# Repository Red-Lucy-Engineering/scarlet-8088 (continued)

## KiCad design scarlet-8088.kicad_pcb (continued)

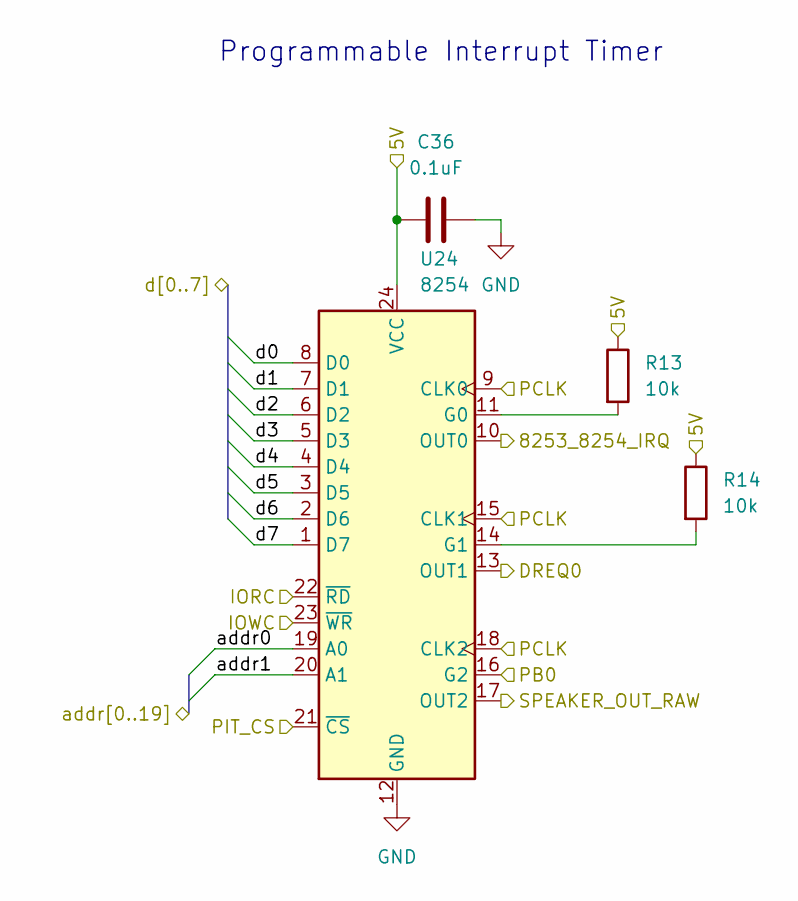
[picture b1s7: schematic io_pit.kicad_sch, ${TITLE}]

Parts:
C36: 0.1uF; C_Disc_D3.0mm_W1.6mm_P2.50mm
R13, R14: 10k; R_Axial_DIN0204_L3.6mm_D1.6mm_P5.08mm_Horizontal
U24: 8254; DIP-24_W15.24mm_Socket

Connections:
/5V: C36.1, R13.1, R14.1, U24.24 (VCC); also elsewhere on the board
/Compute/addr0: U24.19 (A0); also elsewhere on the board
/Compute/addr1: U24.20 (A1); also elsewhere on the board
/Compute/d0: U24.8 (D0); also elsewhere on the board
/Compute/d1: U24.7 (D1); also elsewhere on the board
/Compute/d2: U24.6 (D2); also elsewhere on the board
/Compute/d3: U24.5 (D3); also elsewhere on the board
/Compute/d4: U24.4 (D4); also elsewhere on the board
/Compute/d5: U24.3 (D5); also elsewhere on the board
/Compute/d6: U24.2 (D6); also elsewhere on the board
/Compute/d7: U24.1 (D7); also elsewhere on the board
/IO/8253_8254_IRQ: U24.10 (OUT0); also elsewhere on the board
/IO/PB0: U24.16 (G2); also elsewhere on the board
/IO/PIT_CS: U24.21 (~CS); also elsewhere on the board
/IO/Programmable Interrupt Timer/DREQ0: U24.13 (OUT1)
/IO/Programmable Interrupt Timer/SPEAKER_OUT_RAW: U24.17 (OUT2)
/IORC: U24.22 (~RD); also elsewhere on the board
/IOWC: U24.23 (~WR); also elsewhere on the board
/PCLK: U24.9 (CLK0), U24.15 (CLK1), U24.18 (CLK2); also elsewhere on the board
GND: C36.2, U24.12 (GND); also elsewhere on the board
unnamed: R13.2, U24.11 (G0)
unnamed: R14.2, U24.14 (G1)

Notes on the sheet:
Programmable Interrupt Timer

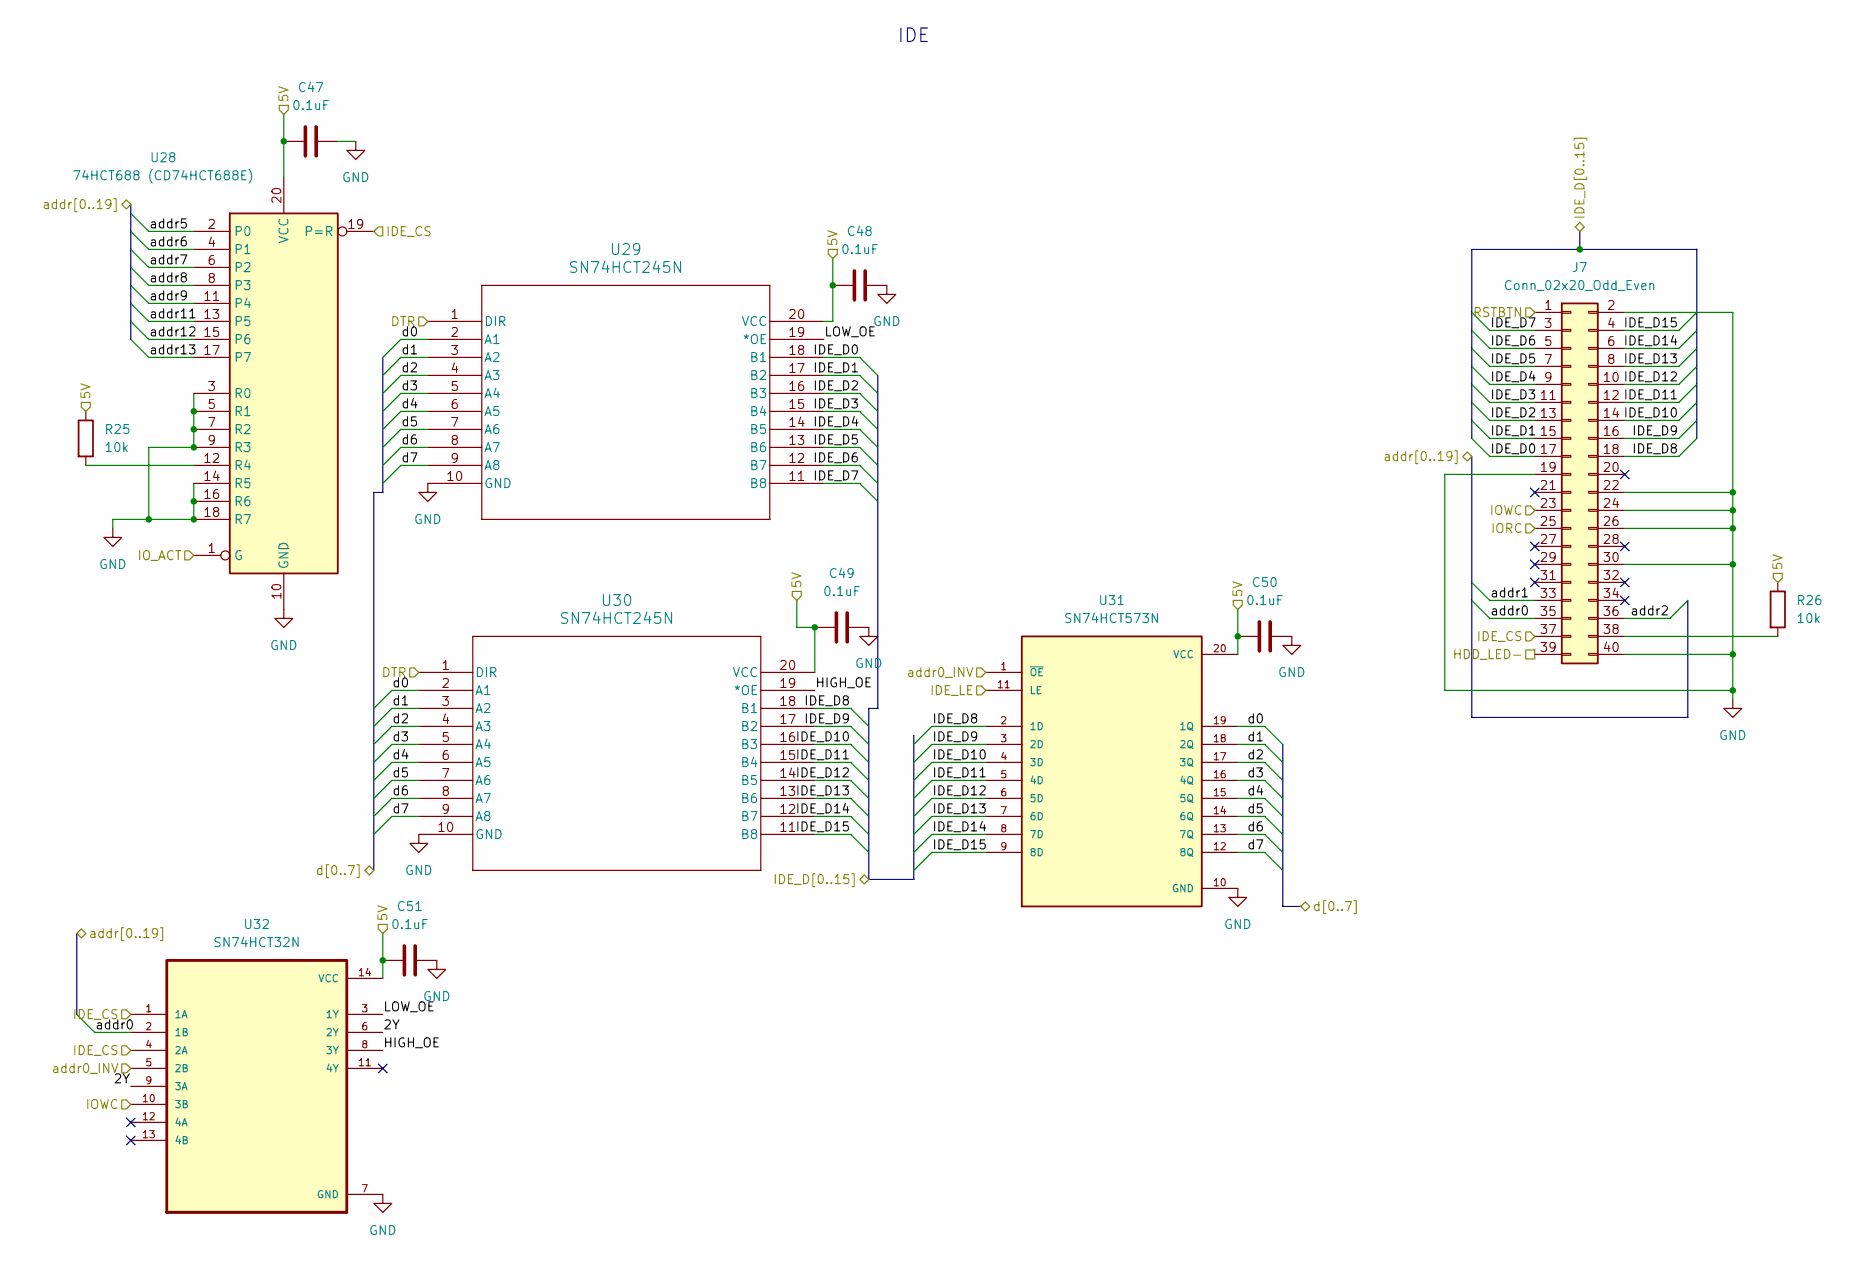
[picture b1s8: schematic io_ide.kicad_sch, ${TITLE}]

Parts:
C47, C48, C49, C50, C51: 0.1uF; C_Disc_D3.0mm_W1.6mm_P2.50mm
J7: Conn_02x20_Odd_Even; IDC-Header_2x20_P2.54mm_Vertical
R25, R26: 10k; R_Axial_DIN0204_L3.6mm_D1.6mm_P5.08mm_Horizontal
U28: 74HCT688 (CD74HCT688E); DIP-20_W7.62mm_Socket
U29, U30: SN74HCT245N
U31: SN74HCT573N; DIP794W45P254L2540H508Q20; PARTREV F
U32: SN74HCT32N; DIP794W45P254L1969H508Q14

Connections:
/5V: C47.1, C48.1, C49.1, C50.1, C51.1, R25.1, R26.1, U28.20 (VCC), U29.20 (VCC), U30.20 (VCC), U31.20 (VCC), U32.14 (VCC); also elsewhere on the board
/Compute/addr0: J7.35, U32.2 (1B); also elsewhere on the board
/Compute/addr1: J7.33; also elsewhere on the board
/Compute/addr2: J7.36; also elsewhere on the board
/Compute/addr5: U28.2 (P0); also elsewhere on the board
/Compute/addr6: U28.4 (P1); also elsewhere on the board
/Compute/addr7: U28.6 (P2); also elsewhere on the board
/Compute/addr8: U28.8 (P3); also elsewhere on the board
/Compute/addr9: U28.11 (P4); also elsewhere on the board
/Compute/addr11: U28.13 (P5); also elsewhere on the board
/Compute/addr12: U28.15 (P6); also elsewhere on the board
/Compute/addr13: U28.17 (P7); also elsewhere on the board
/Compute/d0: U29.2 (A1), U30.2 (A1), U31.19 (1Q); also elsewhere on the board
/Compute/d1: U29.3 (A2), U30.3 (A2), U31.18 (2Q); also elsewhere on the board
/Compute/d2: U29.4 (A3), U30.4 (A3), U31.17 (3Q); also elsewhere on the board
/Compute/d3: U29.5 (A4), U30.5 (A4), U31.16 (4Q); also elsewhere on the board
/Compute/d4: U29.6 (A5), U30.6 (A5), U31.15 (5Q); also elsewhere on the board
/Compute/d5: U29.7 (A6), U30.7 (A6), U31.14 (6Q); also elsewhere on the board
/Compute/d6: U29.8 (A7), U30.8 (A7), U31.13 (7Q); also elsewhere on the board
/Compute/d7: U29.9 (A8), U30.9 (A8), U31.12 (8Q); also elsewhere on the board
/DTR: U29.1 (DIR), U30.1 (DIR); also elsewhere on the board
/HDD_LED-: J7.39; also elsewhere on the board
/IDE_CS: J7.37, U28.19 (P=R), U32.1 (1A), U32.4 (2A); also elsewhere on the board
/IDE_LE: U31.11 (LE); also elsewhere on the board
/IO/IDE/2Y: U32.6 (2Y), U32.9 (3A)
/IO/IDE/HIGH_OE: U30.19 (*OE), U32.8 (3Y)
/IO/IDE/IDE_D0: J7.17, U29.18 (B1)
/IO/IDE/IDE_D1: J7.15, U29.17 (B2)
/IO/IDE/IDE_D2: J7.13, U29.16 (B3)
/IO/IDE/IDE_D3: J7.11, U29.15 (B4)
/IO/IDE/IDE_D4: J7.9, U29.14 (B5)
/IO/IDE/IDE_D5: J7.7, U29.13 (B6)
/IO/IDE/IDE_D6: J7.5, U29.12 (B7)
/IO/IDE/IDE_D7: J7.3, U29.11 (B8)
/IO/IDE/IDE_D8: J7.18, U30.18 (B1), U31.2 (1D)
/IO/IDE/IDE_D9: J7.16, U30.17 (B2), U31.3 (2D)
/IO/IDE/IDE_D10: J7.14, U30.16 (B3), U31.4 (3D)
/IO/IDE/IDE_D11: J7.12, U30.15 (B4), U31.5 (4D)
/IO/IDE/IDE_D12: J7.10, U30.14 (B5), U31.6 (5D)
/IO/IDE/IDE_D13: J7.8, U30.13 (B6), U31.7 (6D)
/IO/IDE/IDE_D14: J7.6, U30.12 (B7), U31.8 (7D)
/IO/IDE/IDE_D15: J7.4, U30.11 (B8), U31.9 (8D)
/IO/IDE/LOW_OE: U29.19 (*OE), U32.3 (1Y)
/IORC: J7.25; also elsewhere on the board
/IOWC: J7.23, U32.10 (3B); also elsewhere on the board
/IO_ACT: U28.1 (G); also elsewhere on the board
/RSTBTN: J7.1; also elsewhere on the board
/addr0_INV: U31.1 (~OE), U32.5 (2B); also elsewhere on the board
GND: C47.2, C48.2, C49.2, C50.2, C51.2, J7.2, J7.19, J7.22, J7.24, J7.26, J7.30, J7.40, U28.3 (R0), U28.5 (R1), U28.7 (R2), U28.9 (R3), U28.10 (GND), U28.14 (R5), U28.16 (R6), U28.18 (R7), U29.10 (GND), U30.10 (GND), U31.10 (GND), U32.7 (GND); also elsewhere on the board
unnamed: J7.38, R26.2
unnamed: R25.2, U28.12 (R4)

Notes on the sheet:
IDE

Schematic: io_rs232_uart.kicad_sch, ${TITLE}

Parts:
C21, C22, C25, C26: 0.1uF; C_Disc_D3.0mm_W1.6mm_P2.50mm
C23, C24: 20pF; C_Disc_D3.0mm_W1.6mm_P2.50mm
C27, C28, C29, C30, C31, C32, C33, C34: 1uF; C_Disc_D3.0mm_W1.6mm_P2.50mm
J3: DE-9SA-J4-2R; DSUB-9_Socket_Horizontal_P2.77x2.84mm_EdgePinOffset7.70mm_H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
R9, R10, R11: 10k; R_Axial_DIN0204_L3.6mm_D1.6mm_P5.08mm_Horizontal
U19: TL16C550BN; DIP-40_W15.24mm_Socket
U20: CD74HCT30E; N14
U21, U22: MAX232; DIP-16_W7.62mm_Socket
Y2: 1.8432MHZ; Crystal_HC49-U_Vertical

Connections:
/5V: C21.1, C22.1, C25.1, C26.1, R9.1, R10.1, U19.40 (VCC), U20.14 (VCC), U21.16 (VCC), U22.16 (VCC); also elsewhere on the board
/Compute/addr0: U19.28 (A0); also elsewhere on the board
/Compute/addr1: U19.27 (A1); also elsewhere on the board
/Compute/addr2: U19.26 (A2); also elsewhere on the board
/Compute/addr3: U20.1 (A); also elsewhere on the board
/Compute/addr4: U20.2 (B); also elsewhere on the board
/Compute/addr5: U20.3 (C); also elsewhere on the board
/Compute/addr6: U20.4 (D); also elsewhere on the board
/Compute/addr7: U20.5 (E); also elsewhere on the board
/Compute/addr8: U20.6 (F); also elsewhere on the board
/Compute/addr9: U20.11 (G); also elsewhere on the board
/Compute/d0: U19.1 (D0); also elsewhere on the board
/Compute/d1: U19.2 (D1); also elsewhere on the board
/Compute/d2: U19.3 (D2); also elsewhere on the board
/Compute/d3: U19.4 (D3); also elsewhere on the board
/Compute/d4: U19.5 (D4); also elsewhere on the board
/Compute/d5: U19.6 (D5); also elsewhere on the board
/Compute/d6: U19.7 (D6); also elsewhere on the board
/Compute/d7: U19.8 (D7); also elsewhere on the board
/IO/RS232 UART/DCD: U19.38 (~DCD), U22.9 (R2OUT)
/IO/RS232 UART/DSR: U19.37 (~DSR), U22.12 (R1OUT)
/IO/RS232 UART/DTR: U19.33 (~DTR), U22.11 (T1IN)
/IO/RS232 UART/UART_CS: R9.2, U19.12 (CS0), U19.13 (CS1), U19.14 (~CS2), U20.8 (*Y)
/IO/UART_IRQ: U19.30 (INTR); also elsewhere on the board
/IORC: U19.21 (~RD); also elsewhere on the board
/IOWC: U19.18 (~WR); also elsewhere on the board
/IO_G2A: U20.12 (H); also elsewhere on the board
/RSTBTN_INV: U19.35 (MR); also elsewhere on the board
GND: C21.2, C22.2, C23.1, C24.1, C25.2, C26.2, C31.1, C32.1, C33.1, C34.1, J3.5, J3.SH (PAD), R11.2, U19.20 (GND), U20.7 (GND), U21.15 (GND), U22.10 (T2IN), U22.15 (GND); also elsewhere on the board
unnamed: R11.1, U19.19 (WR), U19.22 (RD)
unnamed: U19.10 (SIN), U21.12 (R1OUT)
unnamed: U19.11 (SOUT), U21.11 (T1IN)
unnamed: C23.2, U19.16 (XIN), Y2.1
unnamed: C24.2, U19.17 (XOUT), Y2.2
unnamed: U19.36 (~CTS), U21.9 (R2OUT)
unnamed: R10.2, U19.39 (~RI)
unnamed: U19.32 (~RTS), U21.10 (T2IN)
unnamed: C30.2, U21.1 (C1+)
unnamed: C30.1, U21.3 (C1-)
unnamed: C29.2, U21.4 (C2+)
unnamed: C29.1, U21.5 (C2-)
unnamed: J3.2, U21.13 (R1IN)
unnamed: J3.8, U21.8 (R2IN)
unnamed: J3.3, U21.14 (T1OUT)
unnamed: J3.7, U21.7 (T2OUT)
unnamed: C33.2, U21.2 (VS+)
unnamed: C34.2, U21.6 (VS-)
unnamed: C27.2, U22.1 (C1+)
unnamed: C27.1, U22.3 (C1-)
unnamed: C28.2, U22.4 (C2+)
unnamed: C28.1, U22.5 (C2-)
unnamed: J3.6, U22.13 (R1IN)
unnamed: J3.1, U22.8 (R2IN)
unnamed: J3.4, U22.14 (T1OUT)
unnamed: C31.2, U22.2 (VS+)
unnamed: C32.2, U22.6 (VS-)

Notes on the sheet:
UART/RS232 Serial

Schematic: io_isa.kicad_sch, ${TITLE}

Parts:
C52, C53: 2.2uF; CP_Radial_D10.0mm_P2.50mm
C54: 0.1uF; C_Disc_D3.0mm_W1.6mm_P2.50mm
J8, J9, J10: Bus_ISA_8bit; PinSocket_2x31_P2.54mm_Vertical
U33: L7905; TO-220-3_Vertical

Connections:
/5V: J8.3 (VCC), J8.29 (VCC), J9.3 (VCC), J9.29 (VCC), J10.3 (VCC), J10.29 (VCC); also elsewhere on the board
/12V: J8.9 (+12V), J9.9 (+12V), J10.9 (+12V); also elsewhere on the board
/-12V: C52.2, J8.7 (-12V), J9.7 (-12V), J10.7 (-12V), U33.2 (VI); also elsewhere on the board
/ALE: J8.28 (ALE), J9.28 (ALE), J10.28 (ALE); also elsewhere on the board
/CLK: J8.20 (CLK), J9.20 (CLK), J10.20 (CLK); also elsewhere on the board
/Compute/addr0: J8.62 (BA00), J9.62 (BA00), J10.62 (BA00); also elsewhere on the board
/Compute/addr1: J8.61 (BA01), J9.61 (BA01), J10.61 (BA01); also elsewhere on the board
/Compute/addr2: J8.60 (BA02), J9.60 (BA02), J10.60 (BA02); also elsewhere on the board
/Compute/addr3: J8.59 (BA03), J9.59 (BA03), J10.59 (BA03); also elsewhere on the board
/Compute/addr4: J8.58 (BA04), J9.58 (BA04), J10.58 (BA04); also elsewhere on the board
/Compute/addr5: J8.57 (BA05), J9.57 (BA05), J10.57 (BA05); also elsewhere on the board
/Compute/addr6: J8.56 (BA06), J9.56 (BA06), J10.56 (BA06); also elsewhere on the board
/Compute/addr7: J8.55 (BA07), J9.55 (BA07), J10.55 (BA07); also elsewhere on the board
/Compute/addr8: J8.54 (BA08), J9.54 (BA08), J10.54 (BA08); also elsewhere on the board
/Compute/addr9: J8.53 (BA09), J9.53 (BA09), J10.53 (BA09); also elsewhere on the board
/Compute/addr10: J8.52 (BA10), J9.52 (BA10), J10.52 (BA10); also elsewhere on the board
/Compute/addr11: J8.51 (BA11), J9.51 (BA11), J10.51 (BA11); also elsewhere on the board
/Compute/addr12: J8.50 (BA12), J9.50 (BA12), J10.50 (BA12); also elsewhere on the board
/Compute/addr13: J8.49 (BA13), J9.49 (BA13), J10.49 (BA13); also elsewhere on the board
/Compute/addr14: J8.48 (BA14), J9.48 (BA14), J10.48 (BA14); also elsewhere on the board
/Compute/addr15: J8.47 (BA15), J9.47 (BA15), J10.47 (BA15); also elsewhere on the board
/Compute/addr16: J8.46 (BA16), J9.46 (BA16), J10.46 (BA16); also elsewhere on the board
/Compute/addr17: J8.45 (BA17), J9.45 (BA17), J10.45 (BA17); also elsewhere on the board
/Compute/addr18: J8.44 (BA18), J9.44 (BA18), J10.44 (BA18); also elsewhere on the board
/Compute/addr19: J8.43 (BA19), J9.43 (BA19), J10.43 (BA19); also elsewhere on the board
/Compute/d0: J8.40 (DB0), J9.40 (DB0), J10.40 (DB0); also elsewhere on the board
/Compute/d1: J8.39 (DB1), J9.39 (DB1), J10.39 (DB1); also elsewhere on the board
/Compute/d2: J8.38 (DB2), J9.38 (DB2), J10.38 (DB2); also elsewhere on the board
/Compute/d3: J8.37 (DB3), J9.37 (DB3), J10.37 (DB3); also elsewhere on the board
/Compute/d4: J8.36 (DB4), J9.36 (DB4), J10.36 (DB4); also elsewhere on the board
/Compute/d5: J8.35 (DB5), J9.35 (DB5), J10.35 (DB5); also elsewhere on the board
/Compute/d6: J8.34 (DB6), J9.34 (DB6), J10.34 (DB6); also elsewhere on the board
/Compute/d7: J8.33 (DB7), J9.33 (DB7), J10.33 (DB7); also elsewhere on the board
/IO/ISA1_IRQ: J8.4 (IRQ2); also elsewhere on the board
/IO/ISA2_IRQ: J9.23 (IRQ5); also elsewhere on the board
/IO/ISA3_IRQ: J10.21 (IRQ7); also elsewhere on the board
/IO/ISA Slots/-5V: C53.2, C54.1, J8.5 (-5V), J9.5 (-5V), J10.5 (-5V), U33.3 (VO)
/IORC: J8.14 (~IOR), J9.14 (~IOR), J10.14 (~IOR); also elsewhere on the board
/IOWC: J8.13 (~IOW), J9.13 (~IOW), J10.13 (~IOW); also elsewhere on the board
/MRDC: J8.12 (~SMEMR), J9.12 (~SMEMR), J10.12 (~SMEMR); also elsewhere on the board
/MWTC: J8.11 (~SMEMW), J9.11 (~SMEMW), J10.11 (~SMEMW); also elsewhere on the board
/PCLK: J8.30 (OSC), J9.30 (OSC), J10.30 (OSC); also elsewhere on the board
/RSTBTN_INV: J8.2 (RESET), J9.2 (RESET), J10.2 (RESET); also elsewhere on the board
GND: C52.1, C53.1, C54.2, J8.1 (GND), J8.10 (GND), J8.31 (GND), J9.1 (GND), J9.10 (GND), J9.31 (GND), J10.1 (GND), J10.10 (GND), J10.31 (GND), U33.1 (GND); also elsewhere on the board

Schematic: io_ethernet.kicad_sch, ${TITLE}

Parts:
C43, C44, C45, C46: 0.1uF; C_Disc_D3.0mm_W1.6mm_P2.50mm
J6: RJ45_Amphenol_RJMG1BD3B8K1ANR
R22: 10k; R_Axial_DIN0204_L3.6mm_D1.6mm_P5.08mm_Horizontal
R23, R24: 3,3R; R_Axial_DIN0204_L3.6mm_D1.6mm_P5.08mm_Horizontal
U26: Realtek RTL8019AS; PQFP-100_14x20mm_P0.65mm
U27: 93LCxxC; DIP-8_W7.62mm_Socket

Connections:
/5V: C43.1, C44.1, C45.1, C46.1, J6.R4 (TCT), J6.R5 (RCT), R22.1, R23.1, R24.1, U26.6 (VDD), U26.17 (VDD), U26.47 (VDD), U26.57 (VDD), U26.70 (VDD), U26.89 (VDD), U27.8 (VCC); also elsewhere on the board
/Compute/addr0: U26.5 (SA0); also elsewhere on the board
/Compute/addr1: U26.7 (SA1); also elsewhere on the board
/Compute/addr2: U26.8 (SA2); also elsewhere on the board
/Compute/addr3: U26.9 (SA3); also elsewhere on the board
/Compute/addr4: U26.10 (SA4); also elsewhere on the board
/Compute/d0: U26.36 (SD0); also elsewhere on the board
/Compute/d1: U26.37 (SD1); also elsewhere on the board
/Compute/d2: U26.38 (SD2); also elsewhere on the board
/Compute/d3: U26.39 (SD3); also elsewhere on the board
/Compute/d4: U26.40 (SD4); also elsewhere on the board
/Compute/d5: U26.41 (SD5); also elsewhere on the board
/Compute/d6: U26.42 (SD6); also elsewhere on the board
/Compute/d7: U26.43 (SD7); also elsewhere on the board
/IO/RJ45 Ethernet/BCSB: U26.75 (BCSB), U27.2 (SCLK)
/IO/RJ45 Ethernet/EECS: U26.76 (EECS), U27.1 (CS)
/IO/RJ45 Ethernet/EEDI: U26.84 (BD1), U27.4 (DO)
/IO/RJ45 Ethernet/EEDO: U26.85 (BD0), U27.3 (DI)
/IO/RJ45 Ethernet/LED0: J6.L3, U26.61 (LED0)
/IO/RJ45 Ethernet/LED1: J6.L2, U26.62 (LED1)
/IO/RJ45 Ethernet/TPIN_N: J6.R3 (RD+), U26.58 (TPIN-)
/IO/RJ45 Ethernet/TPIN_P: J6.R6 (RD-), U26.59 (TPIN+)
/IO/RJ45 Ethernet/TPOUT_N: J6.R2 (TD-), U26.46 (TPOUT-)
/IO/RJ45 Ethernet/TPOUT_P: J6.R1 (TD+), U26.45 (TPOUT+)
/IO/RTL_IRQ: U26.1 (INT3); also elsewhere on the board
/IORC: U26.29 (IORB); also elsewhere on the board
/IOWC: U26.30 (IOWB); also elsewhere on the board
/RSTBTN: U26.33 (RSTDRV); also elsewhere on the board
GND: C43.2, C44.2, C45.2, C46.2, J6.R8, J6.SH, U26.11 (SA5), U26.12 (SA6), U26.13 (SA7), U26.14 (GND), U26.15 (SA8), U26.16 (SA9), U26.18 (SA10), U26.19 (SA11), U26.20 (SA12), U26.21 (SA13), U26.22 (SA14), U26.23 (SA15), U26.24 (SA16), U26.25 (SA17), U26.26 (SA18), U26.27 (SA19), U26.28 (GND), U26.34 (AEN), U26.44 (GND), U26.52 (GND), U26.83 (GND), U26.86 (GND), U26.87 (SD15), U26.88 (SD14), U26.90 (SD13), U26.91 (SD12), U26.92 (SD11), U26.93 (SD10), U26.94 (SD9), U26.95 (SD8), U27.5 (GND), U27.6 (ORG); also elsewhere on the board
unnamed: J6.L1, R23.2
unnamed: J6.L4, R24.2
unnamed: R22.2, U26.96 (IOCS16B)

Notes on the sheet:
RJ45 Ethernet

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
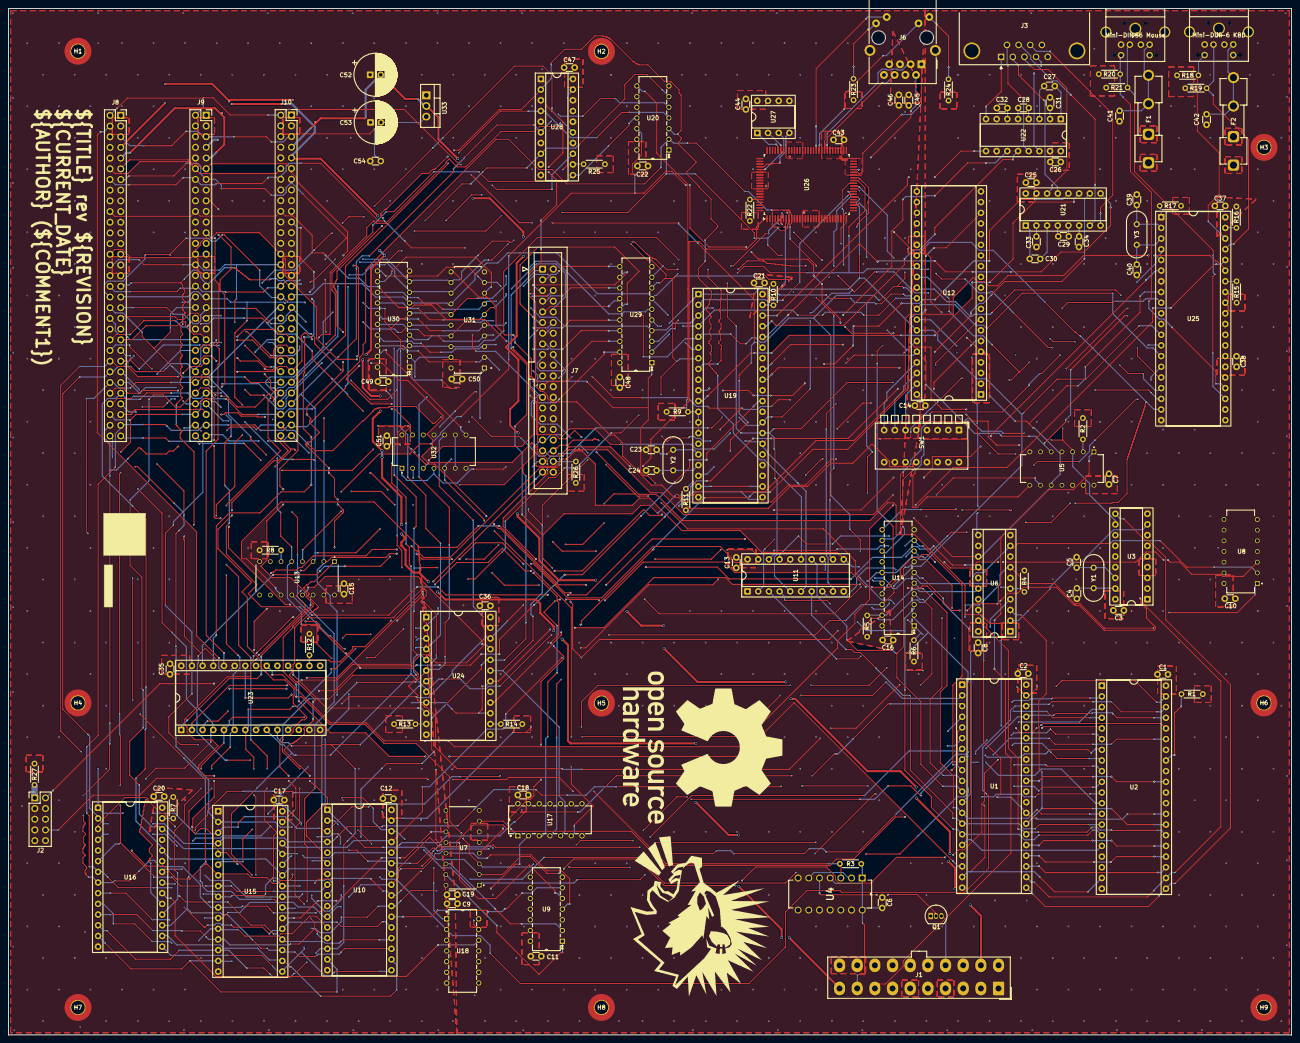
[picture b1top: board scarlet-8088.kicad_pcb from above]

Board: 4 copper layers, 305.0 x 244.0 mm, 140 parts (0 on the bottom side), 183 nets.

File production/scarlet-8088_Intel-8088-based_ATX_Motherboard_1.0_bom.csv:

Designator,Footprint,Quantity,Value,LCSC Part #
"C1, C10, C11, C12, C13, C14, C15, C16, C17, C18, C19, C2, C20, C21, C22, C25, C26, C3, C35, C36, C37, C38, C41, C42, C43, C44, C45, C46, C47, C48, C49, C50, C51, C54, C6, C7, C8, C9",C_Disc_D3.0mm_W1.6mm_P2.50mm,38,0.1uF,
"C23, C24, C39, C4, C40, C5",C_Disc_D3.0mm_W1.6mm_P2.50mm,6,20pF,
"C27, C28, C29, C30, C31, C32, C33, C34",C_Disc_D3.0mm_W1.6mm_P2.50mm,8,1uF,
"C52, C53",CP_Radial_D10.0mm_P2.50mm,2,2.2uF,
"F1, F2",Fuseholder_Clip-5x20mm_Eaton_1A5601-01_Inline_P20.80x6.76mm_D1.70mm_Horizontal,2,Fuse,
J1,Molex_Mini-Fit_Jr_5566-20A_2x10_P4.20mm_Vertical,1,ATX-20,
"J10, J8, J9",PinSocket_2x31_P2.54mm_Vertical,3,Bus_ISA_8bit,
J2,PinHeader_2x05_P2.54mm_Vertical,1,F_PANEL,
J3,DSUB-9_Socket_Horizontal_P2.77x2.84mm_EdgePinOffset7.70mm_Housed_MountingHolesOffset9.12mm,1,DE-9SA-J4-2R,
J4,minidin_6_ps2_pcb_mount,1,Mini-DIN-6 KBD,
J5,minidin_6_ps2_pcb_mount,1,Mini-DIN-6 Mouse,
J6,RJ45_Amphenol_RJMG1BD3B8K1ANR,1,RJ45_Amphenol_RJMG1BD3B8K1ANR,
J7,IDC-Header_2x20_P2.54mm_Vertical,1,Conn_02x20_Odd_Even,
Q1,TO-92_Inline,1,2N7000,
"R1, R10, R11, R12, R13, R14, R15, R16, R17, R2, R22, R25, R26, R3, R4, R5, R6, R7, R8, R9",R_Axial_DIN0204_L3.6mm_D1.6mm_P5.08mm_Horizontal,20,10k,
"R18, R19, R20, R21",R_Axial_DIN0204_L3.6mm_D1.6mm_P5.08mm_Horizontal,4,"4,7k",
"R23, R24, R27",R_Axial_DIN0204_L3.6mm_D1.6mm_P5.08mm_Horizontal,3,"3,3R",
SW1,SW_DIP_SPSTx08_Piano_10.8x21.88mm_W7.62mm_P2.54mm,1,SW_DIP_x08,
U1,DIP-40_W15.24mm_Socket,1,Intel_8088,
"U10, U15",DIP-32_W15.24mm_Socket,2,AS6C4008-55PCN,
U11,DIP-20_W7.62mm_Socket,1,74HCT373,
U12,DIP-40_W15.24mm_Socket,1,8255A,
"U13, U7",DIP794W45P254L1969H508Q16,2,SN74HCT138N,
"U14, U29, U30",SN74HCT245N,3,SN74HCT245N,
U16,DIP-28_W15.24mm_Socket,1,28C256,
U17,CD74HCT14E,1,CD74HCT14E,
U18,N14,1,CD74HCT10E,
U19,DIP-40_W15.24mm_Socket,1,TL16C550BN,
U2,DIP-40_W15.24mm_Socket,1,8087,
U20,N14,1,CD74HCT30E,
"U21, U22",DIP-16_W7.62mm_Socket,2,MAX232,
U23,DIP-28_W15.24mm_Socket,1,8259A,
U24,DIP-24_W15.24mm_Socket,1,8254,
U25,DIP-40_W15.24mm_Socket,1,Intel 8242,
U26,PQFP-100_14x20mm_P0.65mm,1,Realtek RTL8019AS,
U27,DIP-8_W7.62mm_Socket,1,93LCxxC,
U28,DIP-20_W7.62mm_Socket,1,74HCT688 (CD74HCT688E),
U3,DIP-18_W7.62mm_Socket,1,8284,
U31,DIP794W45P254L2540H508Q20,1,SN74HCT573N,
U32,DIP794W45P254L1969H508Q14,1,SN74HCT32N,
U33,TO-220-3_Vertical,1,L7905,
U4,DIP254P762X508-14,1,CD74HCT74E,CD74HCT74E
"U5, U8",DIP794W45P254L1969H508Q14,2,SN74HCT08N,
U6,DIP-20_W7.62mm_Socket,1,8288,
U9,N14,1,CD74HCT21E,
Y1,Crystal_HC49-U_Vertical,1,14.31818 MHz,
Y2,Crystal_HC49-U_Vertical,1,1.8432MHZ,
Y3,Crystal_HC49-U_Vertical,1,12MHz,
